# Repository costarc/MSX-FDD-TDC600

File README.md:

# MSX DC-600
Floppy Disk Controller for MSX nad MSX2 Computers.

Talent TDC-600 clone. PCB redrawn for fit to standard cartridge case.

### YouTube Video
# MSX-TDC-600

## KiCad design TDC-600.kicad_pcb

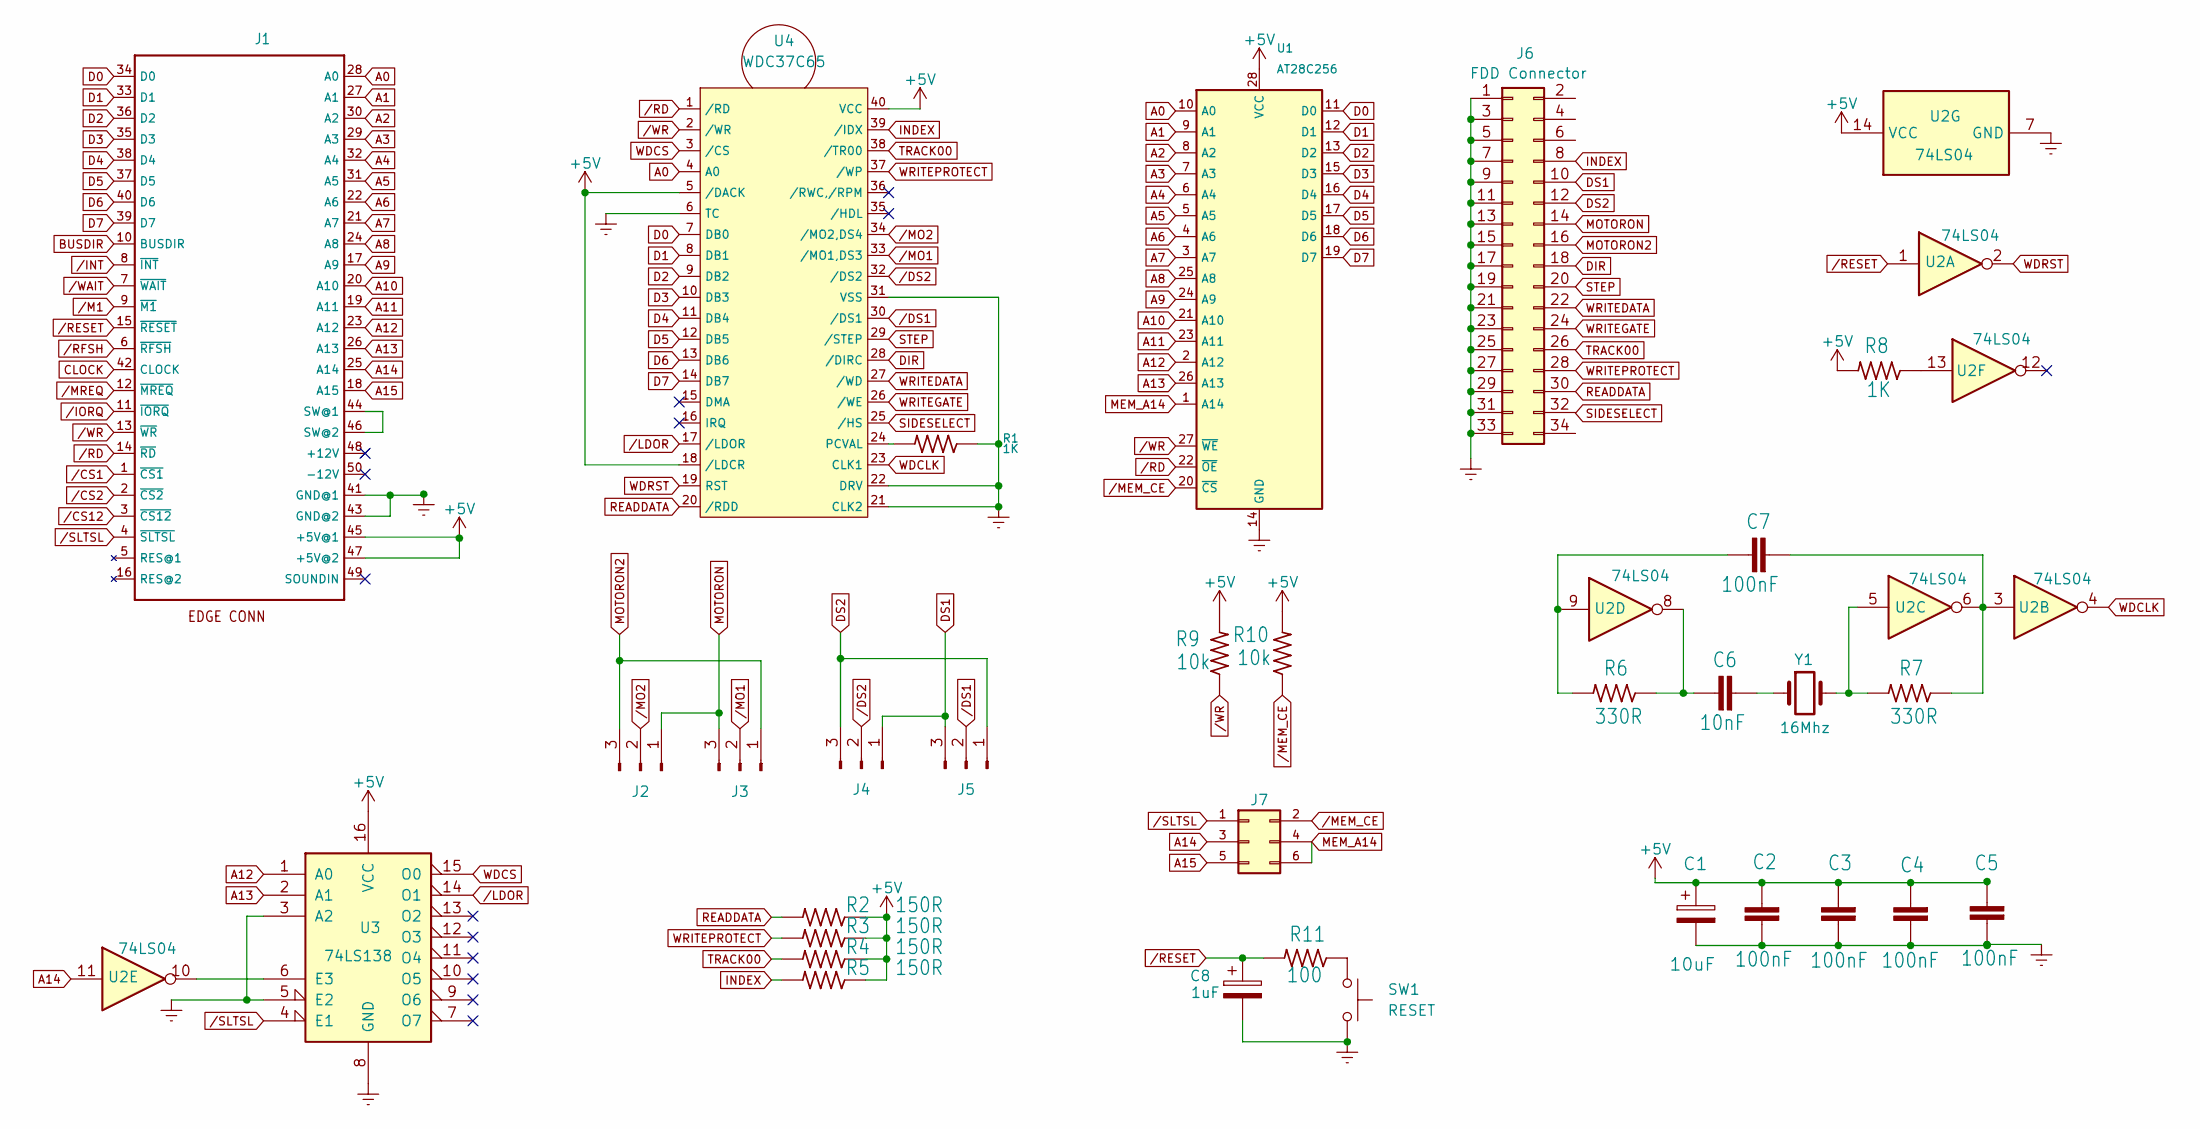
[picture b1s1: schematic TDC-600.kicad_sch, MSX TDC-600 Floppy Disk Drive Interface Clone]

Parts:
C1: 10uF; CP_Radial_D4.0mm_P1.50mm
C2, C3, C4, C5, C7: 100nF; C_Disc_D3.0mm_W1.6mm_P2.50mm
C6: 10nF; C_Disc_D3.0mm_W1.6mm_P2.50mm
C8: 1uF; CP_Radial_D4.0mm_P1.50mm
J1: MSXCART1; MSX_CART_SW_Official
J2, J3, J4, J5: Conn_01x03_Male; PinHeader_1x03_P2.54mm_Vertical
J6: FDD Connector; PinHeader_2x17_P2.54mm_Vertical
J7: ROM_SWITCH; PinHeader_2x03_P2.54mm_Vertical
R1, R8: 1K; R_Axial_DIN0207_L6.3mm_D2.5mm_P7.62mm_Horizontal
R2, R3, R4, R5: 150R; R_Axial_DIN0207_L6.3mm_D2.5mm_P7.62mm_Horizontal
R6, R7: 330R; R_Axial_DIN0207_L6.3mm_D2.5mm_P7.62mm_Horizontal
R9, R10: 10k; R_Axial_DIN0207_L6.3mm_D2.5mm_P7.62mm_Horizontal
R11: 100; R_Axial_DIN0207_L6.3mm_D2.5mm_P7.62mm_Horizontal
SW1: RESET; SW_Tactile_SPST_Angled_PTS645Vx31-2LFS
U1: AT28C256; DIP-28_W15.24mm
U2: 74LS04; DIP-14_W7.62mm
U3: 74LS138; DIP-16_W7.62mm
U4: WDC37C65; DIP-40_W15.24mm
Y1: 16Mhz; Crystal_HC49-U_Vertical

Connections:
+5V: C1.1, C2.2, C3.2, C4.2, C5.2, J1.45 (+5V@1), J1.47 (+5V@2), R2.1, R3.1, R4.1, R5.1, R8.2, R9.2, R10.2, U1.28 (VCC), U2.14 (VCC), U3.16 (VCC), U4.5 (/DACK), U4.18 (/LDCR), U4.40 (VCC)
A0: J1.28 (A0), U1.10 (A0), U4.4 (A0)
A1: J1.27 (A1), U1.9 (A1)
A2: J1.30 (A2), U1.8 (A2)
A3: J1.29 (A3), U1.7 (A3)
A4: J1.32 (A4), U1.6 (A4)
A5: J1.31 (A5), U1.5 (A5)
A6: J1.22 (A6), U1.4 (A6)
A7: J1.21 (A7), U1.3 (A7)
A8: J1.24 (A8), U1.25 (A8)
A9: J1.17 (A9), U1.24 (A9)
A10: J1.20 (A10), U1.21 (A10)
A11: J1.19 (A11), U1.23 (A11)
A12: J1.23 (A12), U1.2 (A12), U3.1 (A0)
A13: J1.26 (A13), U1.26 (A13), U3.2 (A1)
A14: J1.25 (A14), J7.3, U2.11
A15: J1.18 (A15), J7.5
BUSDIR: J1.10 (BUSDIR)
CLOCK: J1.42 (CLOCK)
D0: J1.34 (D0), U1.11 (D0), U4.7 (DB0)
D1: J1.33 (D1), U1.12 (D1), U4.8 (DB1)
D2: J1.36 (D2), U1.13 (D2), U4.9 (DB2)
D3: J1.35 (D3), U1.15 (D3), U4.10 (DB3)
D4: J1.38 (D4), U1.16 (D4), U4.11 (DB4)
D5: J1.37 (D5), U1.17 (D5), U4.12 (DB5)
D6: J1.40 (D6), U1.18 (D6), U4.13 (DB6)
D7: J1.39 (D7), U1.19 (D7), U4.14 (DB7)
DIR: J6.18, U4.28 (/DIRC)
DS1: J4.1, J5.3, J6.10
DS2: J4.3, J5.1, J6.12
GNDREF: C1.2, C2.1, C3.1, C4.1, C5.1, C8.2, J1.41 (GND@1), J1.43 (GND@2), J6.1, J6.3, J6.5, J6.7, J6.9, J6.11, J6.13, J6.15, J6.17, J6.19, J6.21, J6.23, J6.25, J6.27, J6.29, J6.31, J6.33, R1.1, SW1.2, U1.14 (GND), U2.7 (GND), U3.3 (A2), U3.5 (E2), U3.8 (GND), U4.6 (TC), U4.21 (CLK2), U4.22 (DRV), U4.31 (VSS)
INDEX: J6.8, R5.2, U4.39 (/IDX)
MEM_A14: J7.4, J7.6, U1.1 (A14)
MOTORON: J2.1, J3.3, J6.14
MOTORON2: J2.3, J3.1, J6.16
unnamed: C6.1, R6.1, U2.8
unnamed: C6.2, Y1.1
unnamed: C7.1, R6.2, U2.9
unnamed: C7.2, R7.1, U2.3, U2.6
unnamed: J1.44 (SW@1), J1.46 (SW@2)
unnamed: R1.2, U4.24 (PCVAL)
unnamed: R7.2, U2.5, Y1.2
unnamed: R8.1, U2.13
unnamed: R11.1, SW1.1
unnamed: U2.10, U3.6 (E3)
READDATA: J6.30, R2.2, U4.20 (/RDD)
SIDESELECT: U4.25 (/HS)
STEP: J6.20, U4.29 (/STEP)
TRACK00: R4.2, U4.38 (/TR00)
WDCLK: U2.4, U4.23 (CLK1)
WDCS: U3.15 (O0), U4.3 (/CS)
WDRST: U2.2, U4.19 (RST)
WRITEDATA: J6.22, U4.27 (/WD)
WRITEGATE: U4.26 (/WE)
WRITEPROTECT: J6.28, R3.2, U4.37 (/WP)
/CS1: J1.1 (~CS1)
/CS2: J1.2 (~CS2)
/CS12: J1.3 (~CS12)
/DS1: J5.2, U4.30 (/DS1)
/DS2: J4.2, U4.32 (/DS2)
/INT: J1.8 (~INT)
/IORQ: J1.11 (~IORQ)
/LDOR: U3.14 (O1), U4.17 (/LDOR)
/M1: J1.9 (~M1)
/MEM_CE: J7.2, R10.1, U1.20 (~CS)
/MO1: J3.2, U4.33 (/MO1,DS3)
/MO2: J2.2, U4.34 (/MO2,DS4)
/MREQ: J1.12 (~MREQ)
/RD: J1.14 (~RD), U1.22 (~OE), U4.1 (/RD)
/RESET: C8.1, J1.15 (~RESET), R11.2, U2.1
/RFSH: J1.6 (~RFSH)
/SLTSL: J1.4 (~SLTSL), J7.1, U3.4 (E1)
/WAIT: J1.7 (~WAIT)
/WR: J1.13 (~WR), R9.1, U1.27 (~WE), U4.2 (/WR)

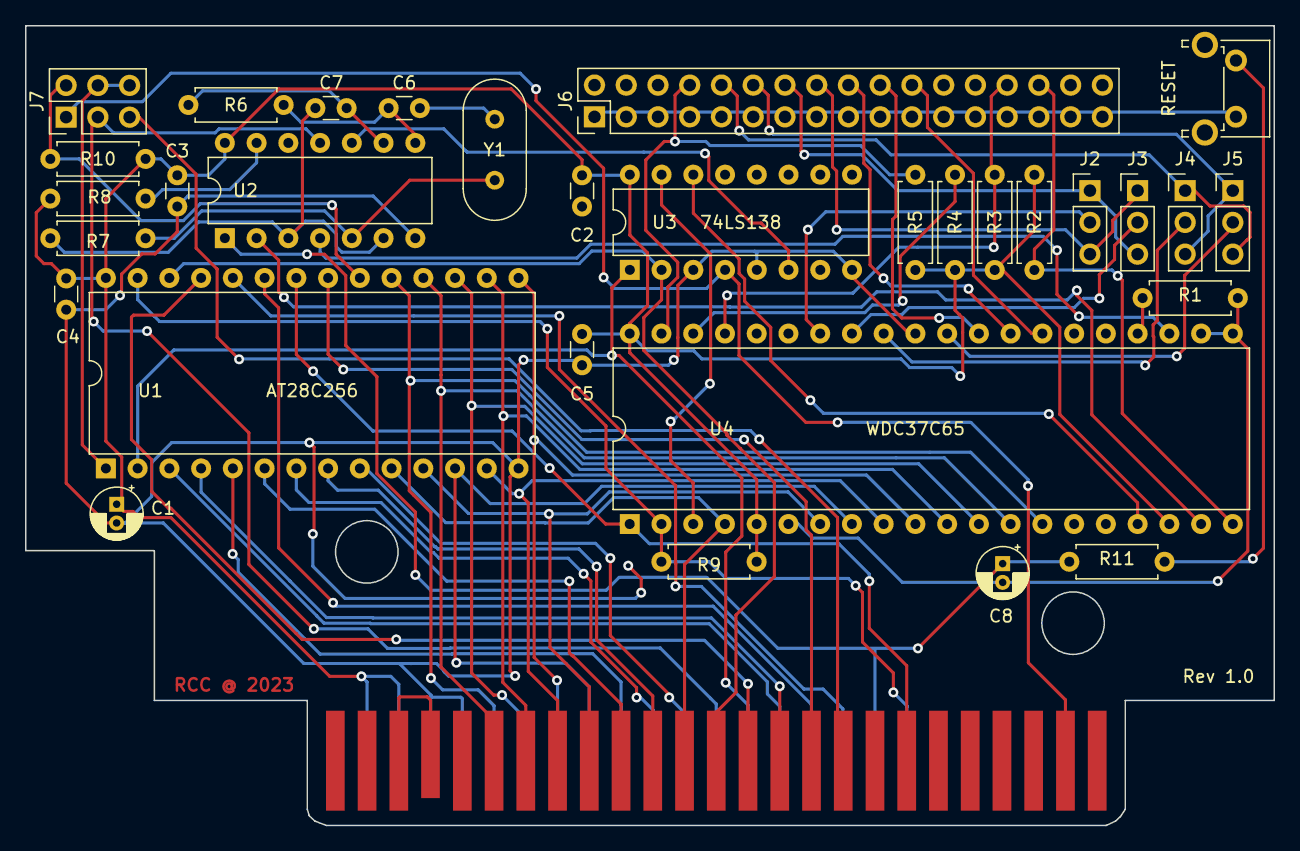
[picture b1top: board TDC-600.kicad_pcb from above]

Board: 2 copper layers, 99.9 x 64.0 mm, 32 parts (0 on the bottom side), 61 nets.

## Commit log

2023-05-28 Initial Redisgn Release 1.0
2023-05-28 Routing Release 1.0
2023-05-28 Routing complete for Rev 1.0
2023-05-28 ~Routing completed, gerbers generated
2023-05-28 add .gitignore
